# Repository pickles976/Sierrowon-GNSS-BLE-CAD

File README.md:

# README

## BOM

RS232 converter 
https://www.digikey.com/en/products/detail/texas-instruments/TRSF3232EIPWR/1909461?s=N4IgTCBcDaICoCUDKAxAzGDBRAkgBQHUEQBdAXyA

ESP32-S3-Mini
https://www.digikey.com/en/products/detail/espressif-systems/ESP32-S3-MINI-1-N4R2/22597234
https://learn.adafruit.com/assets/110822

Power Supply
https://www.digikey.com/en/products/detail/recom-power/RPX-4-0-R/14312389

TODO: which pins from the GPS module do what?

## 12-Pin Connector Pin Assignment

| Header Pin | Signal | Module Pin | GPIO | Notes |
| --- |--------|-----------|------|-------|
| 01 | GND | — | — | Power rail |
| 02 | GND | — | — | Power rail |
| 03 | CS | 34 | IO38 | SPI — cleanest GPIO in range |
| 04 | IO_4 | 38 | IO42 | JTAG-capable, free as GPIO |
| 05 | MISO | 33 | IO37 | SPI — native FSPIQ |
| 06 | IO_3 | 37 | IO41 | JTAG-capable, free as GPIO |
| 07 | MOSI | 31 | IO35 | SPI — native FSPID |
| 08 | IO_2 | 36 | IO40 | JTAG-capable, free as GPIO |
| 09 | SCK | 32 | IO36 | SPI — native FSPICLK |
| 10 | IO_1 | 35 | IO39 | JTAG-capable, free as GPIO |
| 11 | 12V (GNSS Vin) | — | — | Power rail |
| 12 | 3.3V | — | — | Power rail |

> **Note:** Avoid using module pin 26 (IO26) as GPIO — on the N4R2, IO26 is internally tied to PSRAM in QIO mode and will cause corruption if driven externally. Avoid pins 39–40 (GPIO43/44, UART0 TX/RX) and pin 41 (IO45, VDD_SPI strapping pin). Pins 31–33 (IO35–IO37) have eFuse-determined defaults but are free in QIO flash mode. Pins 35–38 (IO39–IO42) are JTAG by default but freely reassignable; USB-JTAG still works regardless.

+12V trace is 2A, needs to be 1.5mm

Cheers
https://documentation.espressif.com/esp32-s3_datasheet_en.pdf#cd-pins-peri-assignment Page 27
https://documentation.espressif.com/esp32-s3-mini-1_mini-1u_datasheet_en.pdf Page 20

Output from GPS module: 9-36V (nominally 12V)
Output from Buck Converter: 3.3V

### Things to Study:
- schematic blocks
- pcb manufacturing
- set up redmine for documentation

```
for all resistors and capacitors you can use 0603 or 0805, diodes can be SMA, LEDs can also be 0603 or 0805, and kicad should have some footprints for some common pushbutton switches.

For the 52uF it would have to be 1206 most likely.. instead of putting +V_OUT its better just to put the actual voltage, like the +3V3 symbol, and then you dont need the power flags as well (unless you want to pass ERC everywhere)
usually you determine footprints for resistors and capacitors based on what is generally available on digi-key and mouser, but mostly they should all be 0603 and 0805
you can also just place a couple 22uF in parallel to get the 52uF since thats a more common size and we can reduce the BOM. Each additional part equates to an additional feeder on a pick and place and costs more to setup
the ESP should have a 22uF near the VIN pin, and you can use that some one 3x on the output of the buck converter

Ok I dont have a lot of time to go through this in detail, but some things I noticed in layout

Try to create more space between the USB-C connector and the ESP's antenna, preferrably swaping places with the USB-C and the 12 pin
Remove the little sliver of ground pour above the antenna, I would just move the ESP32 up more to eliminate that and get it right on the edge of the board.
I would add a lot of stitching vias around the GND pins of the ESP32 to connect the two ground pours on top and bottom.

I personally would recommend a 4-layer stackup so we can have a dedicated 3.3V ground pour and increase overall board capacitance, the ESP's wifi TX events can cause a good inrush current and from an EMI perspective we are creating a large current loops with 3.3V routed the way it is

```

### Workflow Stuff

The DXF files are generated from the full .step file of the BLE adapter. Then we import the outer ring and screw holes as the edge cuts of the board. A DXF containing all lines in the sketch is imported to the "user drawings" layer so we can see where our via holes need to go for the pins.

Layers
1. GND
2. GND
3. +3V3
4. GND

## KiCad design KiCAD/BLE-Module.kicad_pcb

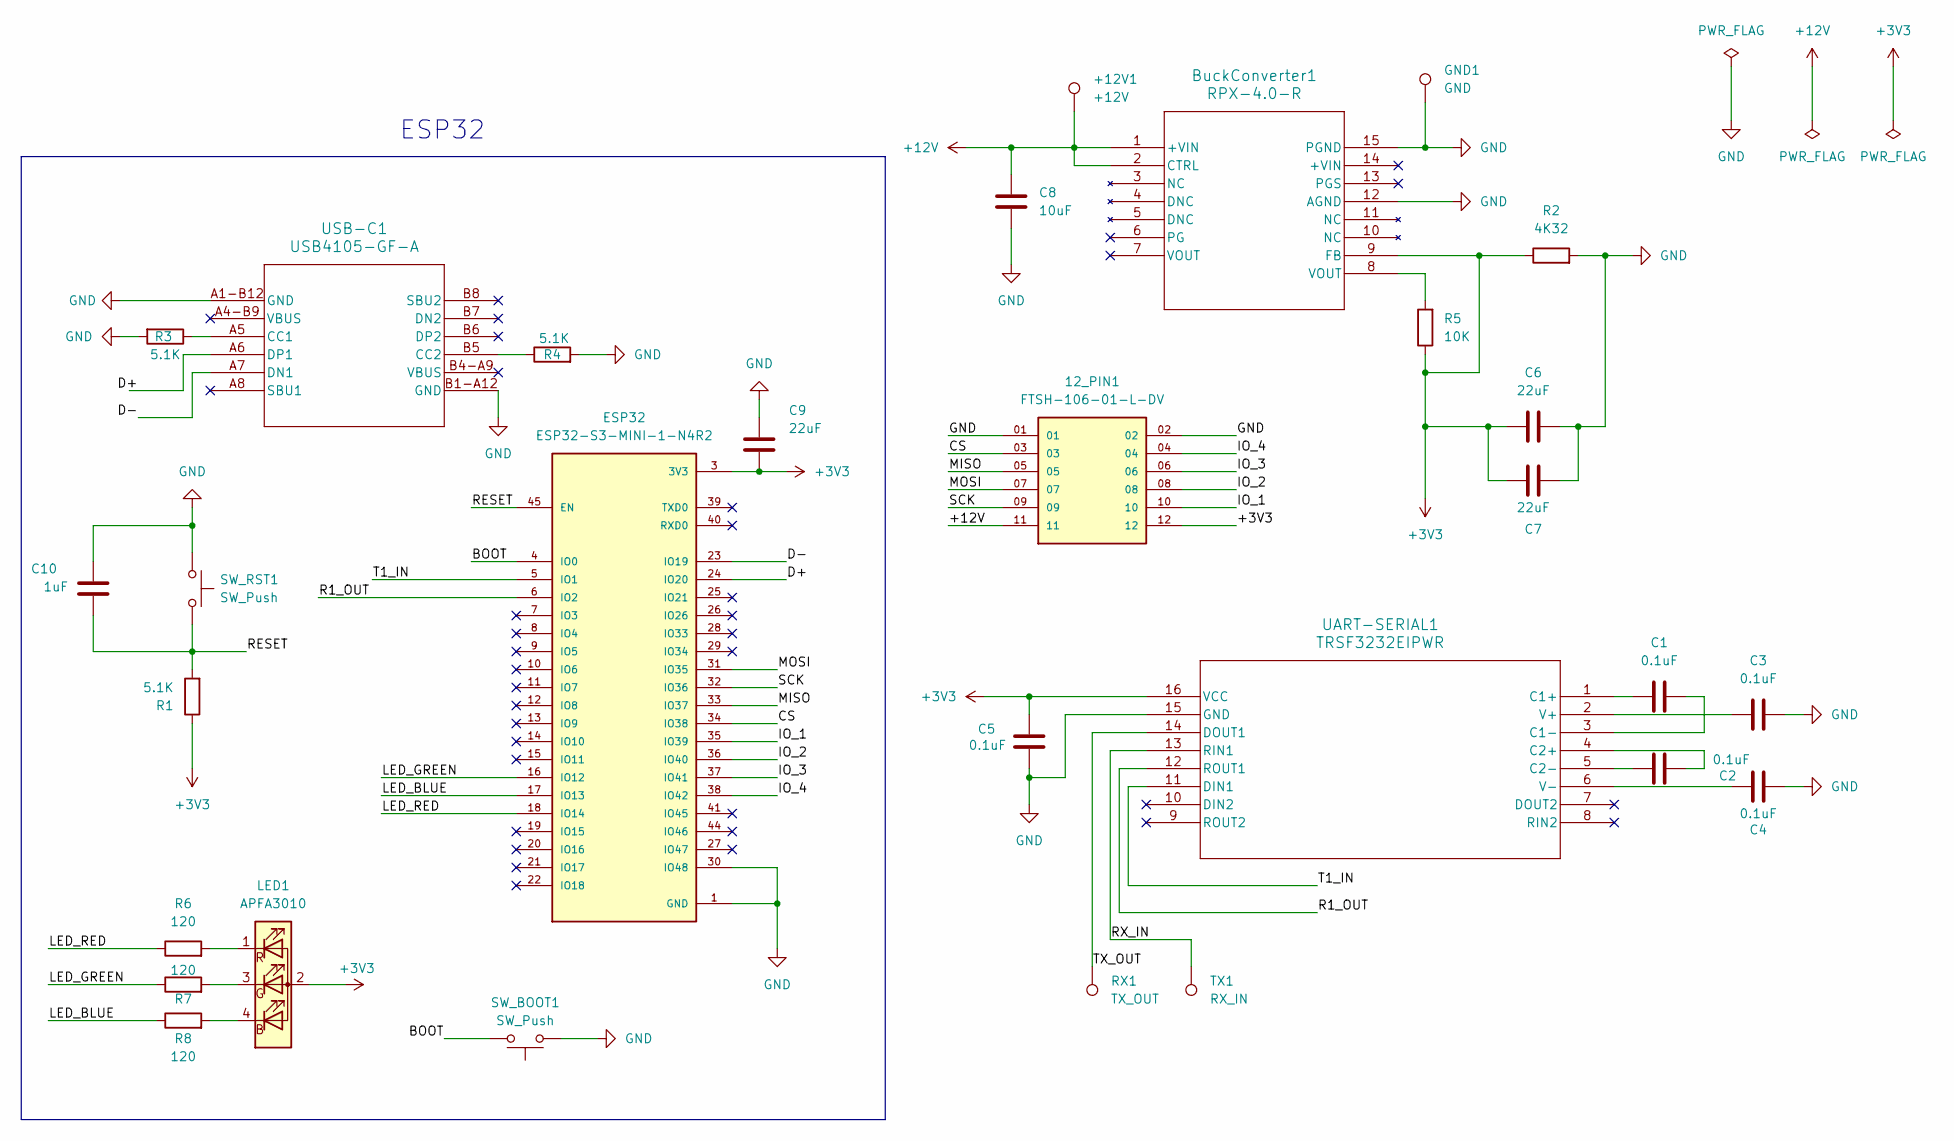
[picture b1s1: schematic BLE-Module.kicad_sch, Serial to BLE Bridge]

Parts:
12_PIN1: FTSH-106-01-L-DV; SAMTEC_FTSH-106-01-L-DV; PARTREV R
+12V1: +12V; TestPoint_THTPad_2.5x2.5mm_Drill1.2mm
BuckConverter1: RPX-4.0-R; RPX-4.0
C1, C2, C3, C4, C5: 0.1uF; C_0603_1608Metric
C6, C7, C9: 22uF; C_1206_3216Metric
C8: 10uF; C_1210_3225Metric
C10: 1uF; C_0603_1608Metric
ESP32: ESP32-S3-MINI-1-N4R2; XCVR_ESP32-S3-MINI-1-N4R2; PARTREV v0.6; DigiKey_Part_Number 1965-ESP32-S3-MINI-1-N4R2CT-ND
GND1: GND; TestPoint_THTPad_2.5x2.5mm_Drill1.2mm
LED1: APFA3010; LED_Kingbright_APFA3010_3x1.5mm_Horizontal
R1, R3, R4: 5.1K; R_0603_1608Metric
R2: 4K32; R_0603_1608Metric
R5: 10K; R_0603_1608Metric
R6, R7, R8: 120; R_0603_1608Metric
RX1: TX_OUT; TestPoint_THTPad_2.5x2.5mm_Drill1.2mm
SW_BOOT1: SW_Push; PTS526_08_CNK
SW_RST1: SW_Push; PTS526_08_CNK
TX1: RX_IN; TestPoint_THTPad_2.5x2.5mm_Drill1.2mm
UART-SERIAL1: TRSF3232EIPWR; PW16
USB-C1: USB4105-GF-A; USB4105_GCT

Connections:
+3V3: 12_PIN1.12, BuckConverter1.9 (FB), C5.1, C6.1, C7.1, C9.2, ESP32.3 (3V3), LED1.2 (A), R1.1, R2.1, R5.1, UART-SERIAL1.16 (VCC); also elsewhere on the board
+12V: 12_PIN1.11, +12V1.1 (1_1), BuckConverter1.1 (+VIN), BuckConverter1.2 (CTRL), C8.1; also elsewhere on the board
/BOOT: ESP32.4 (IO0), SW_BOOT1.2
/CS: 12_PIN1.03, ESP32.34 (IO38)
/D+: ESP32.24 (IO20), USB-C1.A6 (DP1)
/D-: ESP32.23 (IO19), USB-C1.A7 (DN1)
/IO_1: 12_PIN1.10, ESP32.35 (IO39)
/IO_2: 12_PIN1.08, ESP32.36 (IO40)
/IO_3: 12_PIN1.06, ESP32.37 (IO41)
/IO_4: 12_PIN1.04, ESP32.38 (IO42)
/LED_BLUE: ESP32.17 (IO13), R8.1
/LED_GREEN: ESP32.16 (IO12), R7.1
/LED_RED: ESP32.18 (IO14), R6.1
/MISO: 12_PIN1.05, ESP32.33 (IO37)
/MOSI: 12_PIN1.07, ESP32.31 (IO35)
/R1_OUT: ESP32.6 (IO2), UART-SERIAL1.12 (ROUT1)
/RESET: C10.1, ESP32.45 (EN), R1.2, SW_RST1.2
/RX_IN: TX1.1 (1_1), UART-SERIAL1.13 (RIN1)
/SCK: 12_PIN1.09, ESP32.32 (IO36)
/T1_IN: ESP32.5 (IO1), UART-SERIAL1.11 (DIN1)
/TX_OUT: RX1.1 (1_1), UART-SERIAL1.14 (DOUT1)
GND: 12_PIN1.01, 12_PIN1.02, BuckConverter1.12 (AGND), BuckConverter1.15 (PGND), C3.2, C4.2, C5.2, C6.2, C7.2, C8.2, C9.1, C10.2, ESP32.1 (GND), ESP32.2 (GND), ESP32.30 (IO48), ESP32.42 (GND), ESP32.43 (GND), ESP32.46 (GND), ESP32.47 (GND), ESP32.48 (GND), ESP32.49 (GND), ESP32.50 (GND), ESP32.51 (GND), ESP32.52 (GND), ESP32.53 (GND), ESP32.54 (GND), ESP32.55 (GND), ESP32.56 (GND), ESP32.57 (GND), ESP32.58 (GND), ESP32.59 (GND), ESP32.60 (GND), ESP32.61 (GND), ESP32.61_1 (GND), ESP32.61_2 (GND), ESP32.61_3 (GND), ESP32.61_4 (GND), ESP32.61_5 (GND), ESP32.61_6 (GND), ESP32.61_7 (GND), ESP32.61_8 (GND), ESP32.62 (GND), ESP32.63 (GND), ESP32.64 (GND), ESP32.65 (GND), GND1.1 (1_1), R2.2, R3.2, R4.2, SW_BOOT1.1, SW_RST1.1, UART-SERIAL1.15 (GND), USB-C1.A1-B12 (GND), USB-C1.B1-A12 (GND); also elsewhere on the board
unnamed 23: BuckConverter1.8 (VOUT), R5.2; also elsewhere on the board
unnamed: LED1.4 (B), R8.2
unnamed: LED1.3 (G), R7.2
unnamed: LED1.1 (R), R6.2
unnamed: C1.1, UART-SERIAL1.1 (C1+)
unnamed: C1.2, UART-SERIAL1.3 (C1-)
unnamed: C2.2, UART-SERIAL1.4 (C2+)
unnamed: C2.1, UART-SERIAL1.5 (C2-)
unnamed: C3.1, UART-SERIAL1.2 (V+)
unnamed: C4.1, UART-SERIAL1.6 (V-)
unnamed: R3.1, USB-C1.A5 (CC1)
unnamed: R4.1, USB-C1.B5 (CC2)

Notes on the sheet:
ESP32

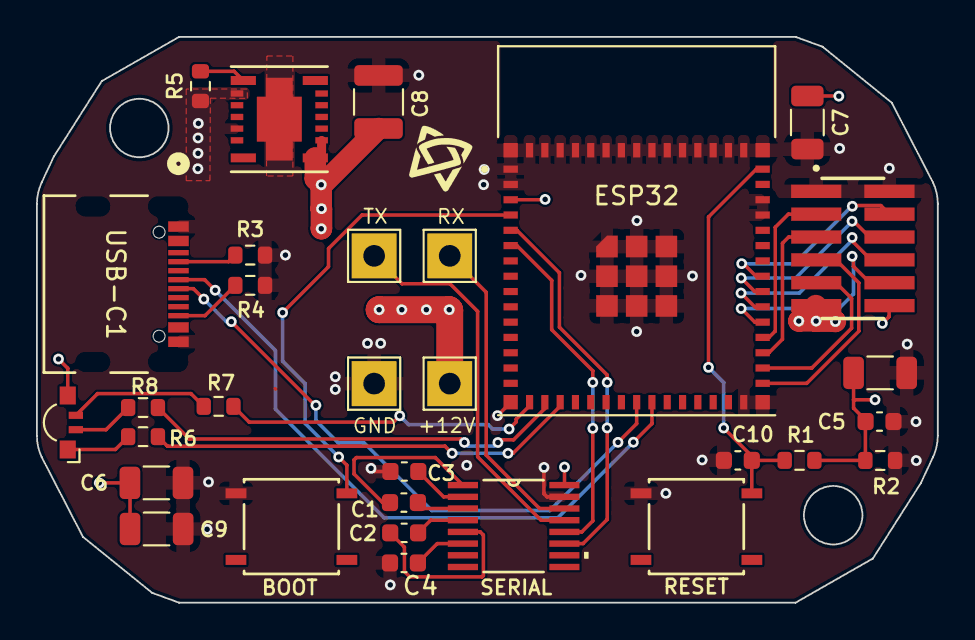
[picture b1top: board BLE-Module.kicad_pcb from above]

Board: 4 copper layers, 50.0 x 31.4 mm, 31 parts (0 on the bottom side), 34 nets.

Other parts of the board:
BuckConverter: RPX-4.0-R; RPX-4.0
C_OUT2: 22uF; C_1206_3216Metric

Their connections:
+3V3: BuckConverter.9 (FB), C_OUT2.1; also elsewhere on the board
+12V: BuckConverter.1 (+VIN), BuckConverter.2 (CTRL); also elsewhere on the board
GND: BuckConverter.12 (AGND), BuckConverter.15 (PGND), C_OUT2.2; also elsewhere on the board
unnamed 23: BuckConverter.8 (VOUT); also elsewhere on the board

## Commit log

2026-04-10 init commit
2026-04-10 lots of feedback
2026-04-15 Redesigned board
2026-04-15 Picked USB-C receptacle
2026-04-15 Added text and graphics
2026-04-15 Added common-anode LED
2026-04-15 updated docs
2026-04-17 Saving before I change the power plane
2026-04-17 Changed design to 4-layer
2026-04-29 Refactored stuff
2026-05-01 Updated pins in readme
2026-05-08 Fixed library paths
